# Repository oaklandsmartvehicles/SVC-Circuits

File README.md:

# SVC-Circuits

## 9/21/20 Revision by: Ben Grudzien
- Added PCB order instructions
- Added pull-down resistor on Mosfet
- Flipped voltage divider resistors
- Made note of changes in schematic

### Open Items:
- Purchase and order PCB
- Purchase stuff on updated BOM: https://docs.google.com/spreadsheets/d/1epTgBYpPCcWoSTmDq_MLOD0yA1EKvYA_yPzVoWDg2d4/edit#gid=490140793

### This is a repository for circuit schematics and PCB designs 
- 'WiringDiagram' = High Level of Hardware components Drive-By-Wire System
- 'ECUPrototypeIO' = Low Level detailed Schematics of Drive-By-Wire System
- 'Conditioning Board' (CB3) = Digital Signal Processing Board (DSP) for ECU to Vehicle 

## 9/9/20 Past Revision by: Ben Grudzien
- Updated PCB to THT components for ease of soldering. Also made some minor layout adjustments
- Noted on the schematic what areas needed to be physically tested
- Updated BOM (Link Below)
- Created new Gerber files for JLCpcb

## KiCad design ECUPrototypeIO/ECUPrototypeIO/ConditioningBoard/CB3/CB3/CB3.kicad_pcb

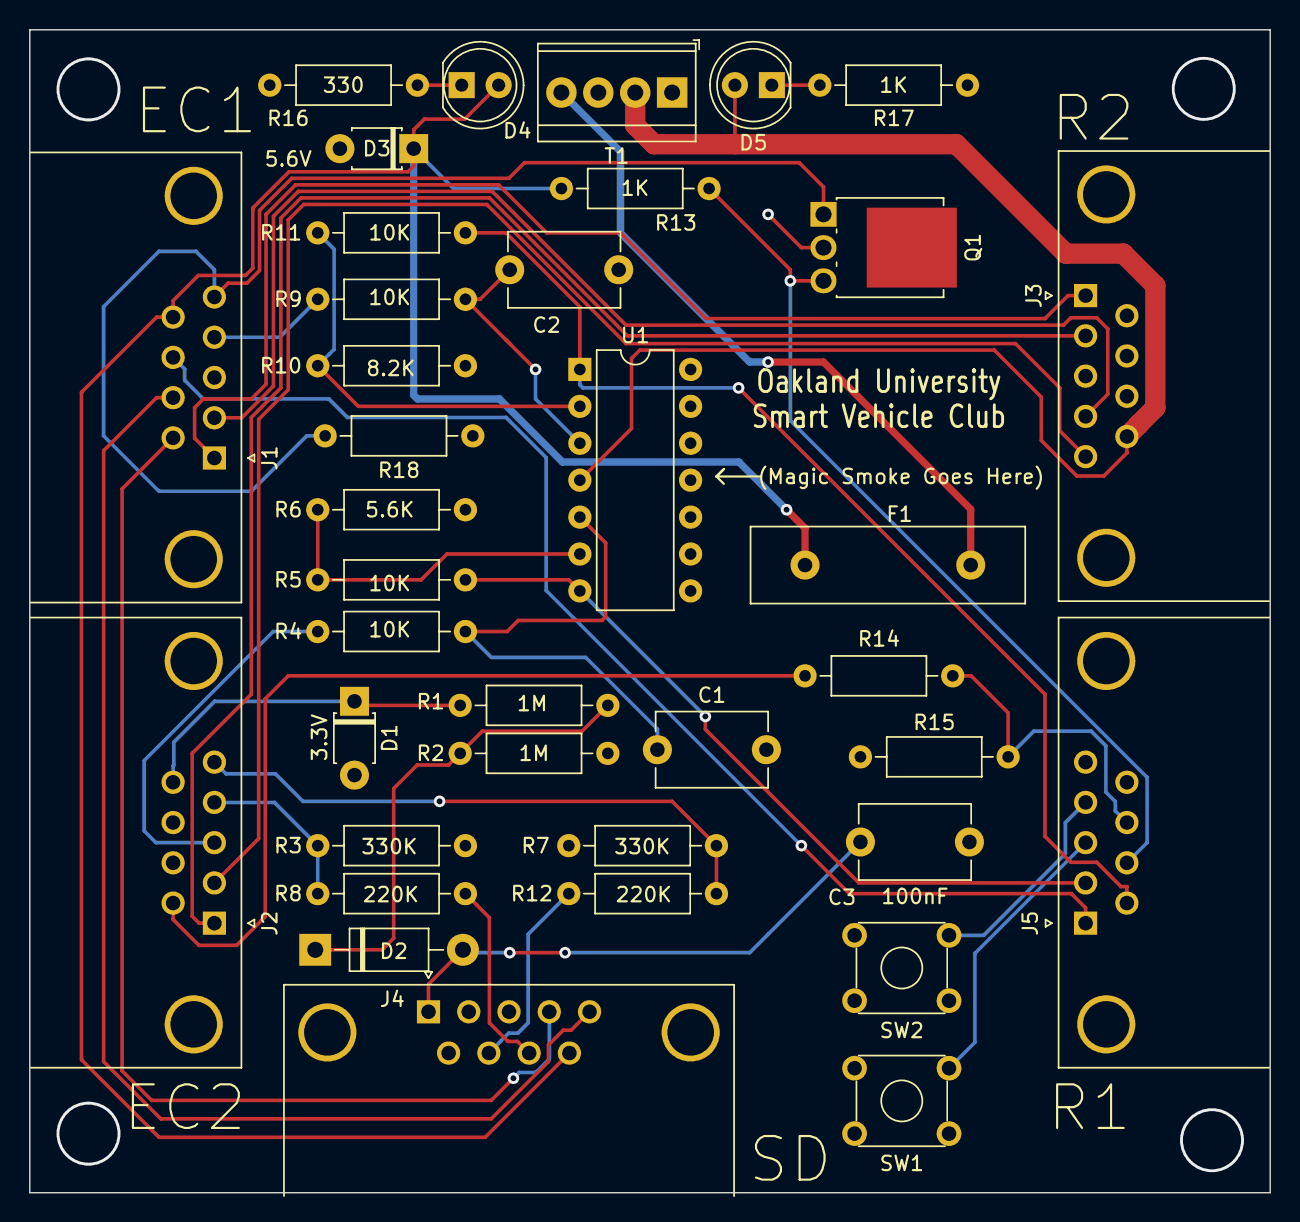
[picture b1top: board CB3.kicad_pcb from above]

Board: 2 copper layers, 85.3 x 80.0 mm, 37 parts (0 on the bottom side), 34 nets.

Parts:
C1, C2, C3: 100nF; C_Disc_D7.5mm_W5.0mm_P7.50mm
D1: 3.3V; D_T-1_P5.08mm_Horizontal
D2: 1N4001; D_DO-41_SOD81_P10.16mm_Horizontal
D3: 5.6V; D_T-1_P5.08mm_Horizontal
D4, D5: LD271; LED_D5.0mm_IRGrey
F1: 1A Fuse; Fuse_Littelfuse-LVR100
J1: ECU Connector 1; DSUB-9_Female_Horizontal_P2.77x2.84mm_EdgePinOffset9.90mm_H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
J2: ECU Connector 2; DSUB-9_Female_Horizontal_P2.77x2.84mm_EdgePinOffset9.90mm_H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
J3: Relay Module Con2; DSUB-9_Female_Horizontal_P2.77x2.84mm_EdgePinOffset9.90mm_H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
J4: Vehicle Connector 1; DSUB-9_Male_Horizontal_P2.77x2.84mm_EdgePinOffset9.90mm_Hou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
J5: Relay Module Con1; DSUB-9_Male_Horizontal_P2.77x2.84mm_EdgePinOffset9.90mm_Hou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
Q1: 2N7002H; SIPAK-1EP_Horizontal_TabDown
R1, R2: 1M; R_Axial_DIN0207_L6.3mm_D2.5mm_P10.16mm_Horizontal
R3, R7: 330K; R_Axial_DIN0207_L6.3mm_D2.5mm_P10.16mm_Horizontal
R4, R5, R9, R11, R15: 10K; R_Axial_DIN0207_L6.3mm_D2.5mm_P10.16mm_Horizontal
R6: 5.6K; R_Axial_DIN0207_L6.3mm_D2.5mm_P10.16mm_Horizontal
R8, R12: 220K; R_Axial_DIN0207_L6.3mm_D2.5mm_P10.16mm_Horizontal
R10: 8.2K; R_Axial_DIN0207_L6.3mm_D2.5mm_P10.16mm_Horizontal
R13: 1k; R_Axial_DIN0207_L6.3mm_D2.5mm_P10.16mm_Horizontal
R14: 39K; R_Axial_DIN0207_L6.3mm_D2.5mm_P10.16mm_Horizontal
R16: 330; R_Axial_DIN0207_L6.3mm_D2.5mm_P10.16mm_Horizontal
R17: 1K; R_Axial_DIN0207_L6.3mm_D2.5mm_P10.16mm_Horizontal
R18: 10k; R_Axial_DIN0207_L6.3mm_D2.5mm_P10.16mm_Horizontal
SW1, SW2: MomentarySwitch; SW_TH_Tactile_Omron_B3F-10xx
T1: Screw_Terminal_01x04; TerminalBlock_TE_282834-4_1x04_P2.54mm_Horizontal
U1: LM324; DIP-14_W7.62mm

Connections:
5V: F1.2, T1.4
5V_Fused: D3.1, D4.2, F1.1, J1.9, J4.9, R13.2
12V: D5.2, J3.9, T1.2, U1.4
Acceleration: J1.4, R9.2
AccelerationEnable: J1.5, Q1.1, R18.2
Brake: J1.8, J5.1
ESTOP: J2.6, R14.2
GND: C1.2, C2.2, C3.2, D1.2, D3.2, J1.0, J1.3, J2.0, J3.0, J3.3, J4.0, J4.2, J4.3, J4.6, J5.0, Q1.2, R2.1, R3.2, R6.2, R7.2, R10.2, R15.1, R16.2, R17.2, R18.1, SW1.2, SW2.2, T1.1, T1.3, U1.11
MotorSpeed_Red: C3.1, D2.2, J4.1
unnamed: C1.1, R4.1, U1.5
unnamed: C2.1, R9.1, U1.3
unnamed: D2.1, R1.1, R2.2
unnamed: D4.1, R16.1
unnamed: D5.1, R17.1
unnamed: R5.2, R6.1, U1.6
unnamed: R10.1, R11.2, U1.2
RelayC_NO: J5.6, R11.1, U1.1
RelayD_NO: J5.7, Q1.3, R13.1
ReverseControl_Blue: J1.7, J4.5
ReverseControl_Red: J1.6, J4.4
SE_A: J4.8, R8.1
SE_B: J4.7, R12.1
SafetyLights1Enable: J1.1, J3.1
SafetyLights1_Mode: J5.3, SW1.3
SafetyLights2Enable: J1.2, J3.4
SafetyLights2_Mode: J5.4, SW2.3
SteeringDirection: J2.1, J3.2
SteeringDriverConnector1_Yellow: J5.2, R5.1, U1.7
SteeringEnable: J2.2, J3.5
SteeringEncoderA: J2.4, R3.1, R8.2
SteeringEncoderB: J2.5, R7.1, R12.2
SteeringPower: J2.3, R4.2
VehicleSpeed: D1.1, J2.9, R1.2
VoltageDivider_C: J5.8, R14.1, R15.2

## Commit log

2019-11-29 rev2
2020-01-11 Adds WiringDiagram
2020-01-11 Adds schematic info
2020-01-11 Update PDF
2020-01-13 Sam's Edits (Early January)
2020-01-23 ECU Low Level Schematic Edit
2020-02-08 Finishes pinouts and moves them to the Wiring Daigram
2020-02-08 Fixed the mosfet schematic
2020-02-08 Make the new rev pdf
2020-02-22 Encoder Pins Added to VC1 & VC2 Pins were rearranged
2020-02-29 created signal conditioning board schematic for PCB. Footprints need to be revised
2020-03-08 Fixed Reverse Control on Wiring Diagram, Fixed relevant errors on PCB Schematic 'CB3', Added footprints to all components on 'CB3', and added all parts to PCB Layout
2020-03-09 grouped relevant components on PCB Schematic
2020-03-10 1st Draft PCB completed; Import dsn file to view complete layout
2020-03-10 Fixes relay wiring mismatch
2020-03-10 Not exactly sure what I changed.
2020-08-30 latest files from jb laptop, unsure what changes exist
2020-09-03 inverted RelaysIN F & H Label in 'Wiring Diagram' and Relay Connector 2 and cleaned ECU Prototype Schematic
2020-09-05 Cleaned Up Diagram, Added I/O Spreadsheet for Diagnostics and Validation
2020-09-10 Look at README File
2020-09-19 Updates to I.O Spreadsheet
2020-09-21 Completed I.O Spreadsheet
2020-09-21 Look at README
